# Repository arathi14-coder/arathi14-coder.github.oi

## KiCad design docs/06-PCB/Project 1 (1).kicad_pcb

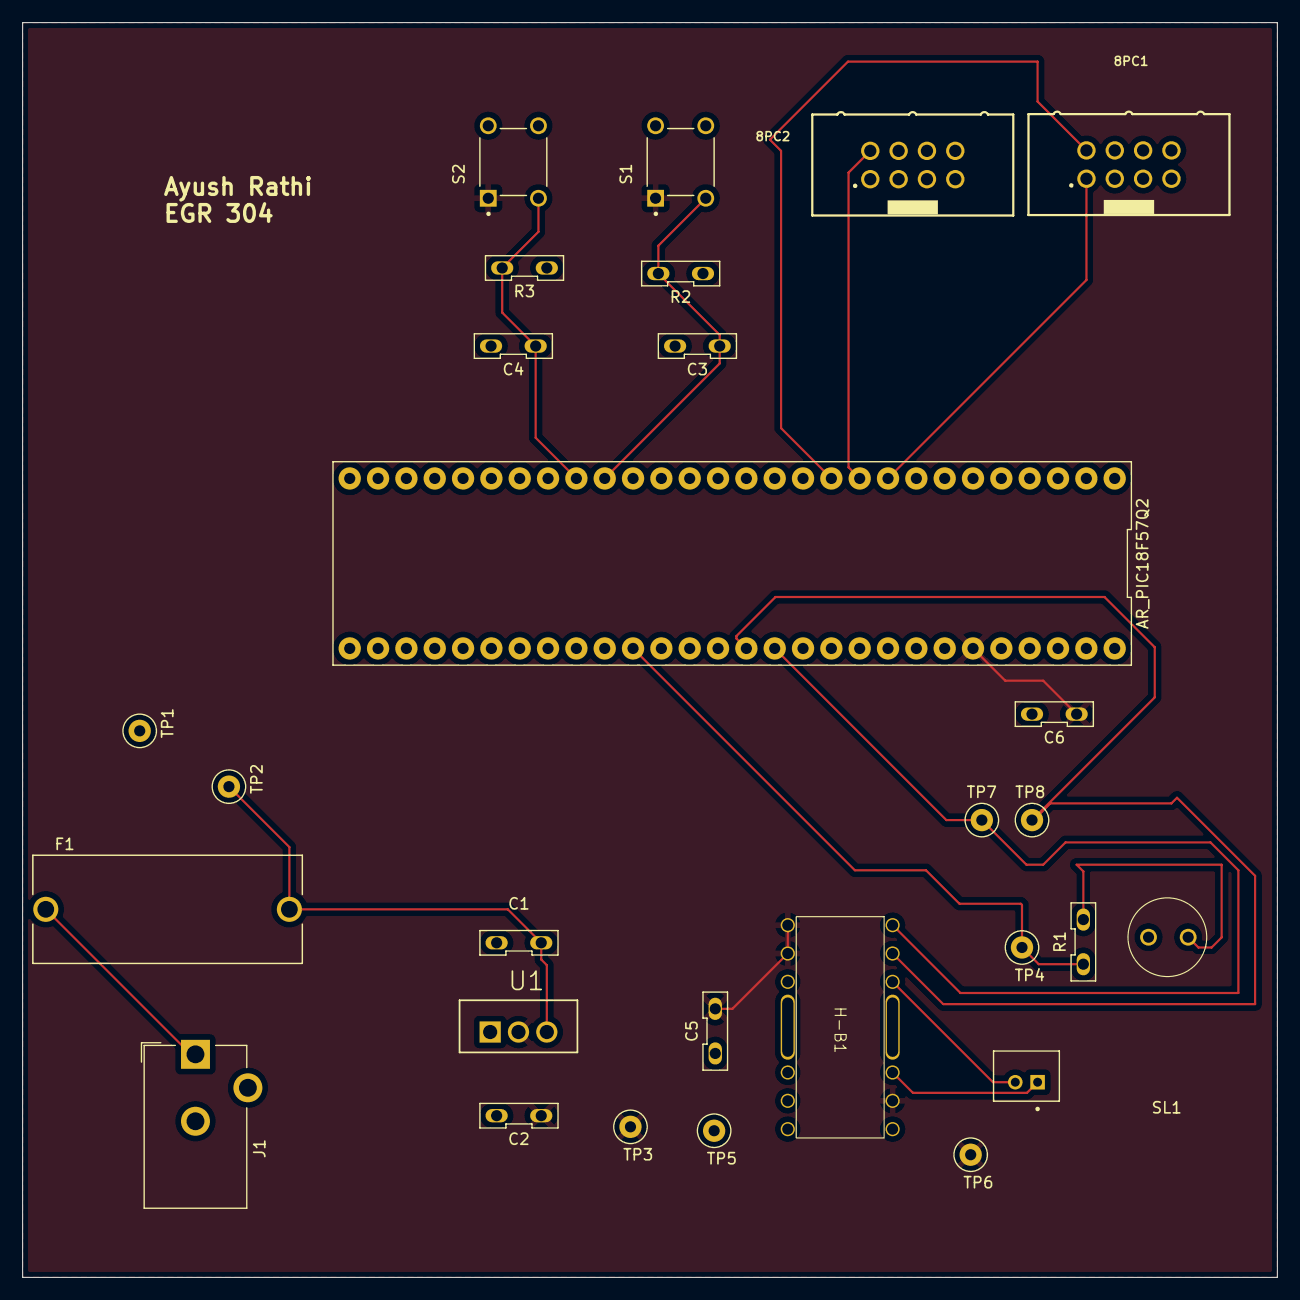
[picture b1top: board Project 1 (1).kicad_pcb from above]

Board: 2 copper layers, 112.5 x 112.5 mm, 28 parts (0 on the bottom side), 15 nets.

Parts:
8PC1, 8PC2: 8pin
AR_PIC18F57Q2: DIP-56_600 (1)
C1: 10uf; Rus
C2: 50uf; Rus
C3, C4: 0.10uf; Rus
C5: 100uf; Rus
C6: 0.1uf; Rus
D1: LED; LED_5MM
F1: 2A; FUSE_4527
H-B1: HB-1
J1: Barrel_Jack_Switch; BarrelJack_CUI_PJ-102AH_Horizontal
R1: 330 Ohms 0.25W; Rus
R2, R3: 10K; Rus
S1, S2: TS02-66-50-BK-160-SCR-D; SW_TS02-66-50-BK-160-SCR-D
SL1: sol
TP1, TP2, TP3, TP4, TP5, TP6: TestPoint; TestPoint_Loop_D2.50mm_Drill1.0mm
TP7, TP8: TestPoint_Loop_D2.50mm_Drill1.0mm
U1: LM1085IT-5.0; TO254P470X1016X2222-3P

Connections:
+5V: AR_PIC18F57Q2.51 (VTG), C2.1, C5.2, C6.1, H-B1.5 (PVCCB), H-B1.6 (VCC), H-B1.8 (PVCCA), S1.1, S2.1, TP3.1, TP6.1, U1.2 (VOUT)
/9V+ main: C1.1, F1.2, TP2.1, U1.3 (VIN)
/CRT_INT: 8PC2.2, AR_PIC18F57Q2.10 (RB1)
/EXT_pin: 8PC1.2, AR_PIC18F57Q2.11 (RC4)
/MIC_INT: 8PC1.1, AR_PIC18F57Q2.9 (RB2)
/MIC_OUT1: AR_PIC18F57Q2.43 (RA0), H-B1.11 (FWD), TP8.1
/MIC_OUT2: AR_PIC18F57Q2.44 (RA1), H-B1.12 (REVERSEB), TP7.1
/Open button: AR_PIC18F57Q2.19 (RC7), C3.1, R2.2, S1.3
/Red LED: AR_PIC18F57Q2.39 (RD5), R1.1, TP4.1
/close button: AR_PIC18F57Q2.20 (RD0), C4.1, R3.2, S2.3
GNDREF: 8PC1.8, 8PC2.8, AR_PIC18F57Q2.15 (GND), AR_PIC18F57Q2.24 (GND), AR_PIC18F57Q2.33 (GND), AR_PIC18F57Q2.42 (GND), AR_PIC18F57Q2.52 (GND), AR_PIC18F57Q2.55 (V0FF), C1.2, C2.2, C3.2, C4.2, C5.1, C6.2, D1.1 (K), H-B1.FIN (GND), H-B1.GND, J1.2, R2.1, R3.1, TP1.1, TP5.1, U1.1 (ADJ/GND)
unnamed: D1.2 (A), R1.2
unnamed: F1.1, J1.1
unnamed: H-B1.9 (OUT1A), SL1.1
unnamed: H-B1.10 (OUT2A), SL1.2

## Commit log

2025-09-06 changes for the power md
2025-09-06 index update
2025-10-07 Rename pages.yml to main.yml
2025-10-07 deploy: 500226afb70343c8074b8070bd8a3a399b8fb9e8
2025-10-07 deploy: 4815306a5aece0be7d9b25722a056422f1a6f6f6
2025-10-07 deploy: c9e80ebef7724f769982e4ccfb1ed6c79b732160
2025-10-07 deploy: d6f5064283d432ee15b716360f34f28f8d24bc49
2025-10-07 deploy: a5f7fabca7ef358acccef44bf5b91e144ab31287
2025-10-07 deploy: 6a56488dd3746ce38070b191f67b71636117a7ea
2025-10-07 deploy: 529097707dbb9b2804dbda98aae4fbabe97ada5d
2025-10-07 deploy: e63e89097309faaebbaf512cf0724589687bc156
2025-10-26 deploy: a127837a89af0f3aaf4902c8dd268d194681655a
2025-10-26 deploy: f904b510b326a0a79612cb12f49a3751737e63a7
2025-10-27 deploy: 8882c7924158e7df143087a93d1270bc257f564f
2025-10-27 deploy: 295acae340bf120a5105ca538b3bd8708b9c1de7
2025-10-27 deploy: 7be07080fc13f646478303ddbe387b1bff46ca1d
2025-10-27 deploy: 7c276fff2117ee80977e43a5cffa5c0ff1812afb
2025-10-27 deploy: 11e594c16799c40bbf71d09252c4df98745af0fe
2025-10-27 deploy: 31cb5b951d11faf438a4b457aa39867b649e3e74
2025-10-27 deploy: 461506d8bbf5508f006873dc070d0e394352e3f5
2025-10-27 deploy: 8fd60ddd9fce9d97fd64fdf5165a97d8b9d29c2d
2025-10-27 deploy: 26031dc6feba5c2c506b34df7d20d41bc6c852df
2025-10-27 deploy: 8d3b303d56f616f19464e0ab3ffbfac868c377c1
2025-10-27 deploy: e0701c392e086ddfac0a0bfc75022a50d50d1e9b
2025-10-27 deploy: 4953f4778ab865c159a50cb4dcbb6cace028b905
2025-10-27 deploy: 87b7baa75cd86725df23e31a9106b04f1c2a49ac
2025-10-27 deploy: 3ec3abc6651b0fbec990d82c30f2c1c2dc6c291f
2025-10-27 deploy: 05062cd469f07d6de8bd64ac38f1b94634ac3bd5
2025-10-27 deploy: 876bd3861f294af88504c0840597561e2bbb80fc
2025-10-27 deploy: 54df02e2927b12bfdb8d931a8e095844b7e5816e
2025-10-27 deploy: a3936f353a88a3f525e5b006dde9b704098697ab
2025-11-08 deploy: 606b6a8efd2776d6876df4c220e223048171a33d
2025-11-08 deploy: 22e18b97c65cc7fc96e1fe288a2d4aa8f2b04c7e
2025-11-08 deploy: da6ae930e72be82df2ab2d3fb579f4854aac4fb4
2025-12-08 deploy: c8f45c10c8a7ff72e1bfaded9eb7502624a865a7
2025-12-09 deploy: a0f0e558df9636d12885a3dbf4043816f9a22d29
2025-12-09 deploy: 5eb39a29d31c9b330b765cdaec601335b5a35ba9
2025-12-09 deploy: 01985fe1976745b8ff1d81667a765007c5ce8e5f
2025-12-09 deploy: ffbb321061aeb509116c81d0b3df6ad261d62423
2025-12-09 deploy: 56e691c9ee78925ddc77970a89ecde74be6ed34d
2025-12-09 deploy: 7571037836e5e78042f2ddea8e1c9bcf2af12fa2
2025-12-09 deploy: 9e9ac2f3dd22921a30f995b1e53b8acfc96cc13c
2025-12-09 deploy: 8866f521201a5168bdf15fc3de7e1bbece6c3d97
2025-12-09 deploy: af1c2f686e630af998893f2662940381c523015c
2025-12-09 deploy: d3b784e5ec4378c76d2131a169f33144cac4da1f
2025-12-09 deploy: be1b585a1fdda512766d794370fe8fb7f55dd3f1
2025-12-09 deploy: 00f85439f0046417d8aef6c2604b1eaec4a6b01a
2025-12-09 Create PCB
2025-12-09 deploy: ed5bb73d98878c45dd177d103114eb7b917d9675
2025-12-09 deploy: e30f4832755d3ca586afe3f436a35f95fb3f435c
2025-12-09 Create PCB File
2025-12-09 deploy: d34d7775451a9b202552dd493de4c135a1a5ca62
2025-12-09 Update PCB File
2025-12-09 deploy: 66ed3be1fa205e69ad1cba5a6af244ff9813bf6e
2025-12-09 deploy: 842ae953ac68af8f06598e3cefeb1ac360d9189e
2025-12-09 deploy: a4df18247db3e005a0e533d29fcc2944ce4af16c
2025-12-09 deploy: b269c314c36dd0a6435792889ac015b55a7f24bb
2025-12-09 deploy: ce91bb4025bc528f5c318ba3b23577bf78eed7a1
2025-12-09 deploy: cdf503bfdff2ab5db4cb2836252c4646df15fae7
2025-12-09 deploy: e4c1cc1099862465d1020adec080345a693445db
2025-12-09 deploy: 78983f7d8b2a3920fb16c92c22ce98124431ea3d
2025-12-09 deploy: 38d8a1146b012fd0069f737c27aaf05f480e9eb2
2025-12-09 change
2025-12-09 deploy: 7a60a4e585e9664b72917c7ed84d8fc9a569939e
2025-12-09 deploy: 96359af45b6b39b406c2c708564a6beb5d61851b
2025-12-09 deploy: 076f5cb259a621803fe4aa96ca8a75fd4dae9611
2025-12-09 deploy: 74935d1888af747054a46c454ed534eb2dc96393
2025-12-09 deploy: 37e6ba1020a1bbf106ed75c1706e7c36b0198941
2025-12-09 deploy: ddcc023628c0f8d56f1edf2e69bf297f0a178072
2025-12-09 deploy: a9b4cede68e3f91a7b89d5bab09e753616ff0590
